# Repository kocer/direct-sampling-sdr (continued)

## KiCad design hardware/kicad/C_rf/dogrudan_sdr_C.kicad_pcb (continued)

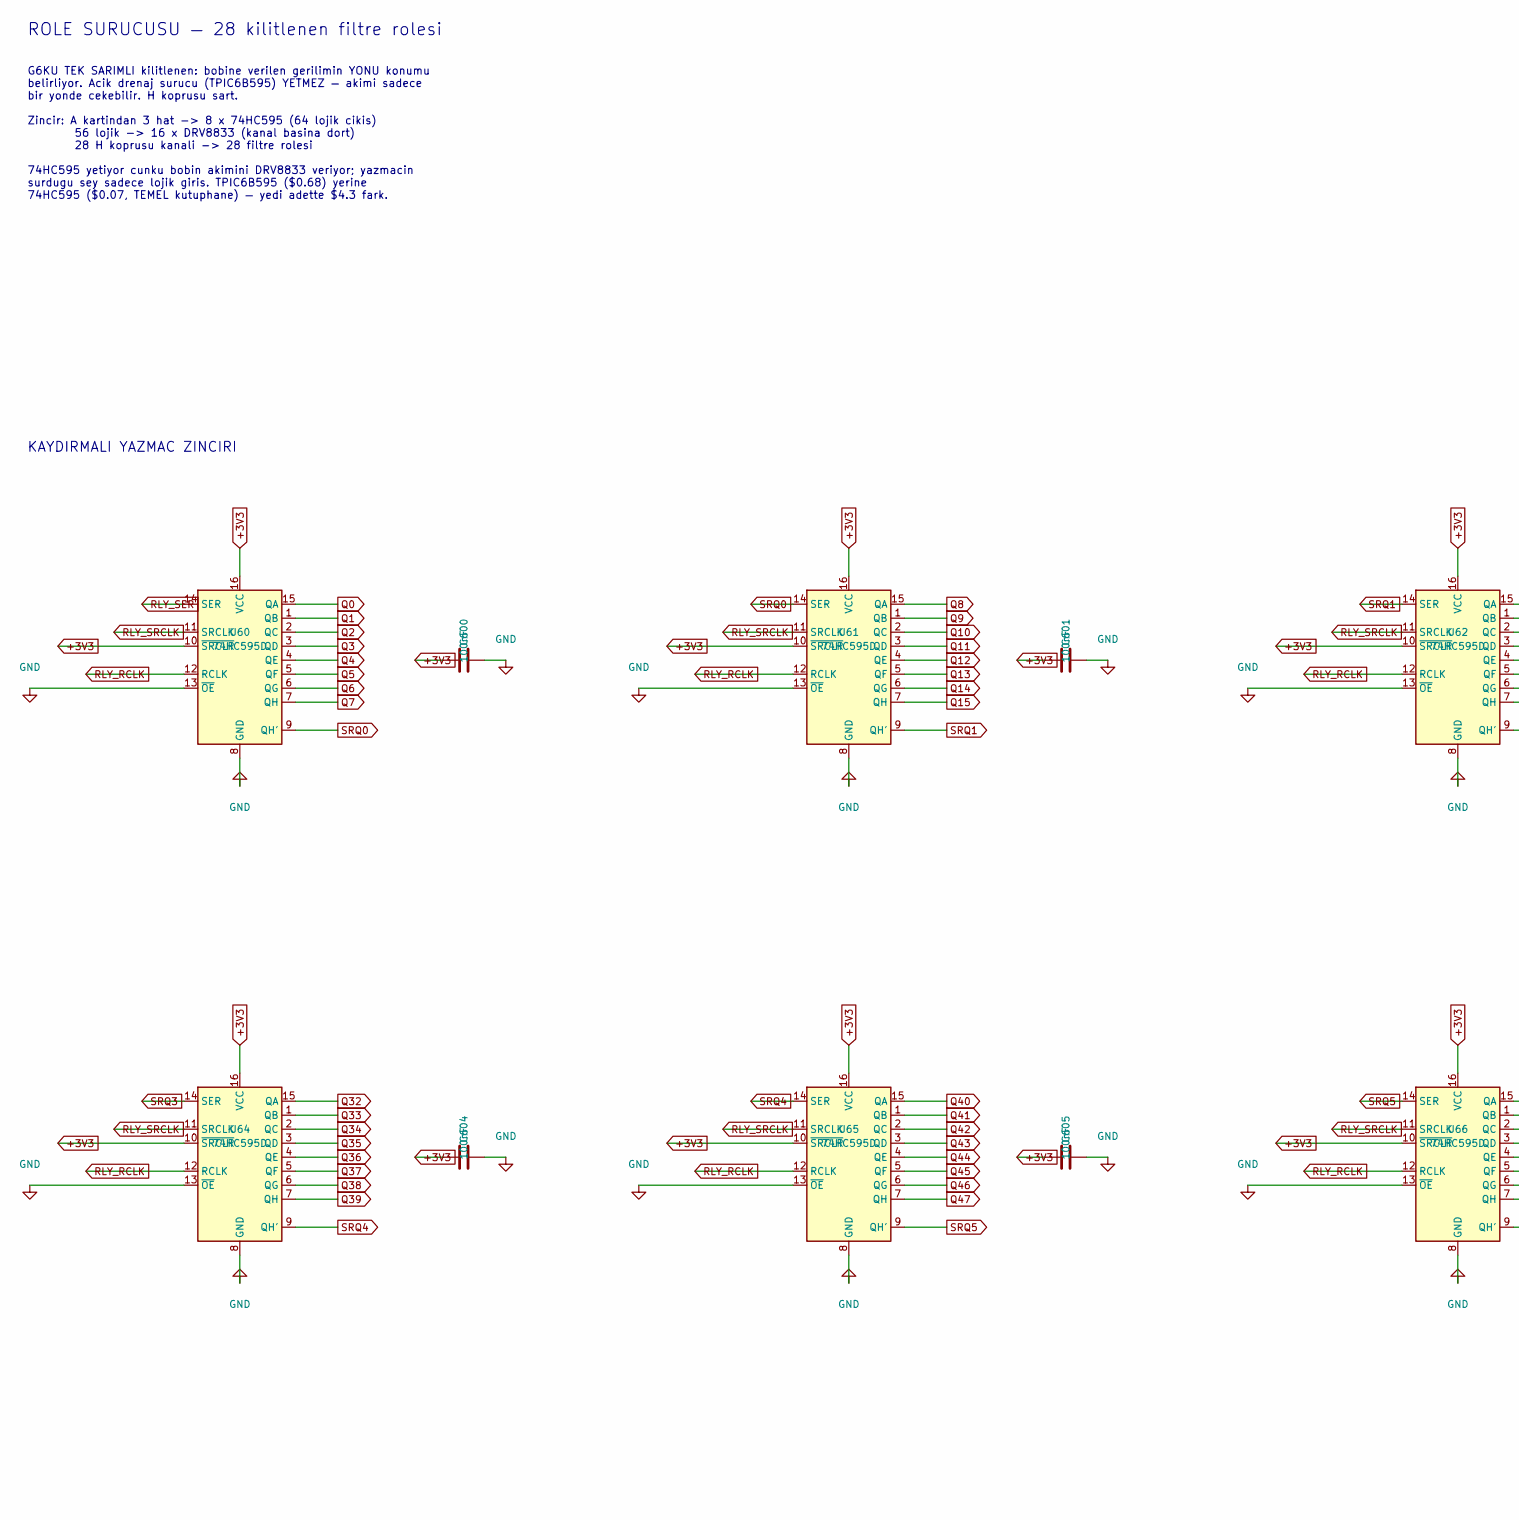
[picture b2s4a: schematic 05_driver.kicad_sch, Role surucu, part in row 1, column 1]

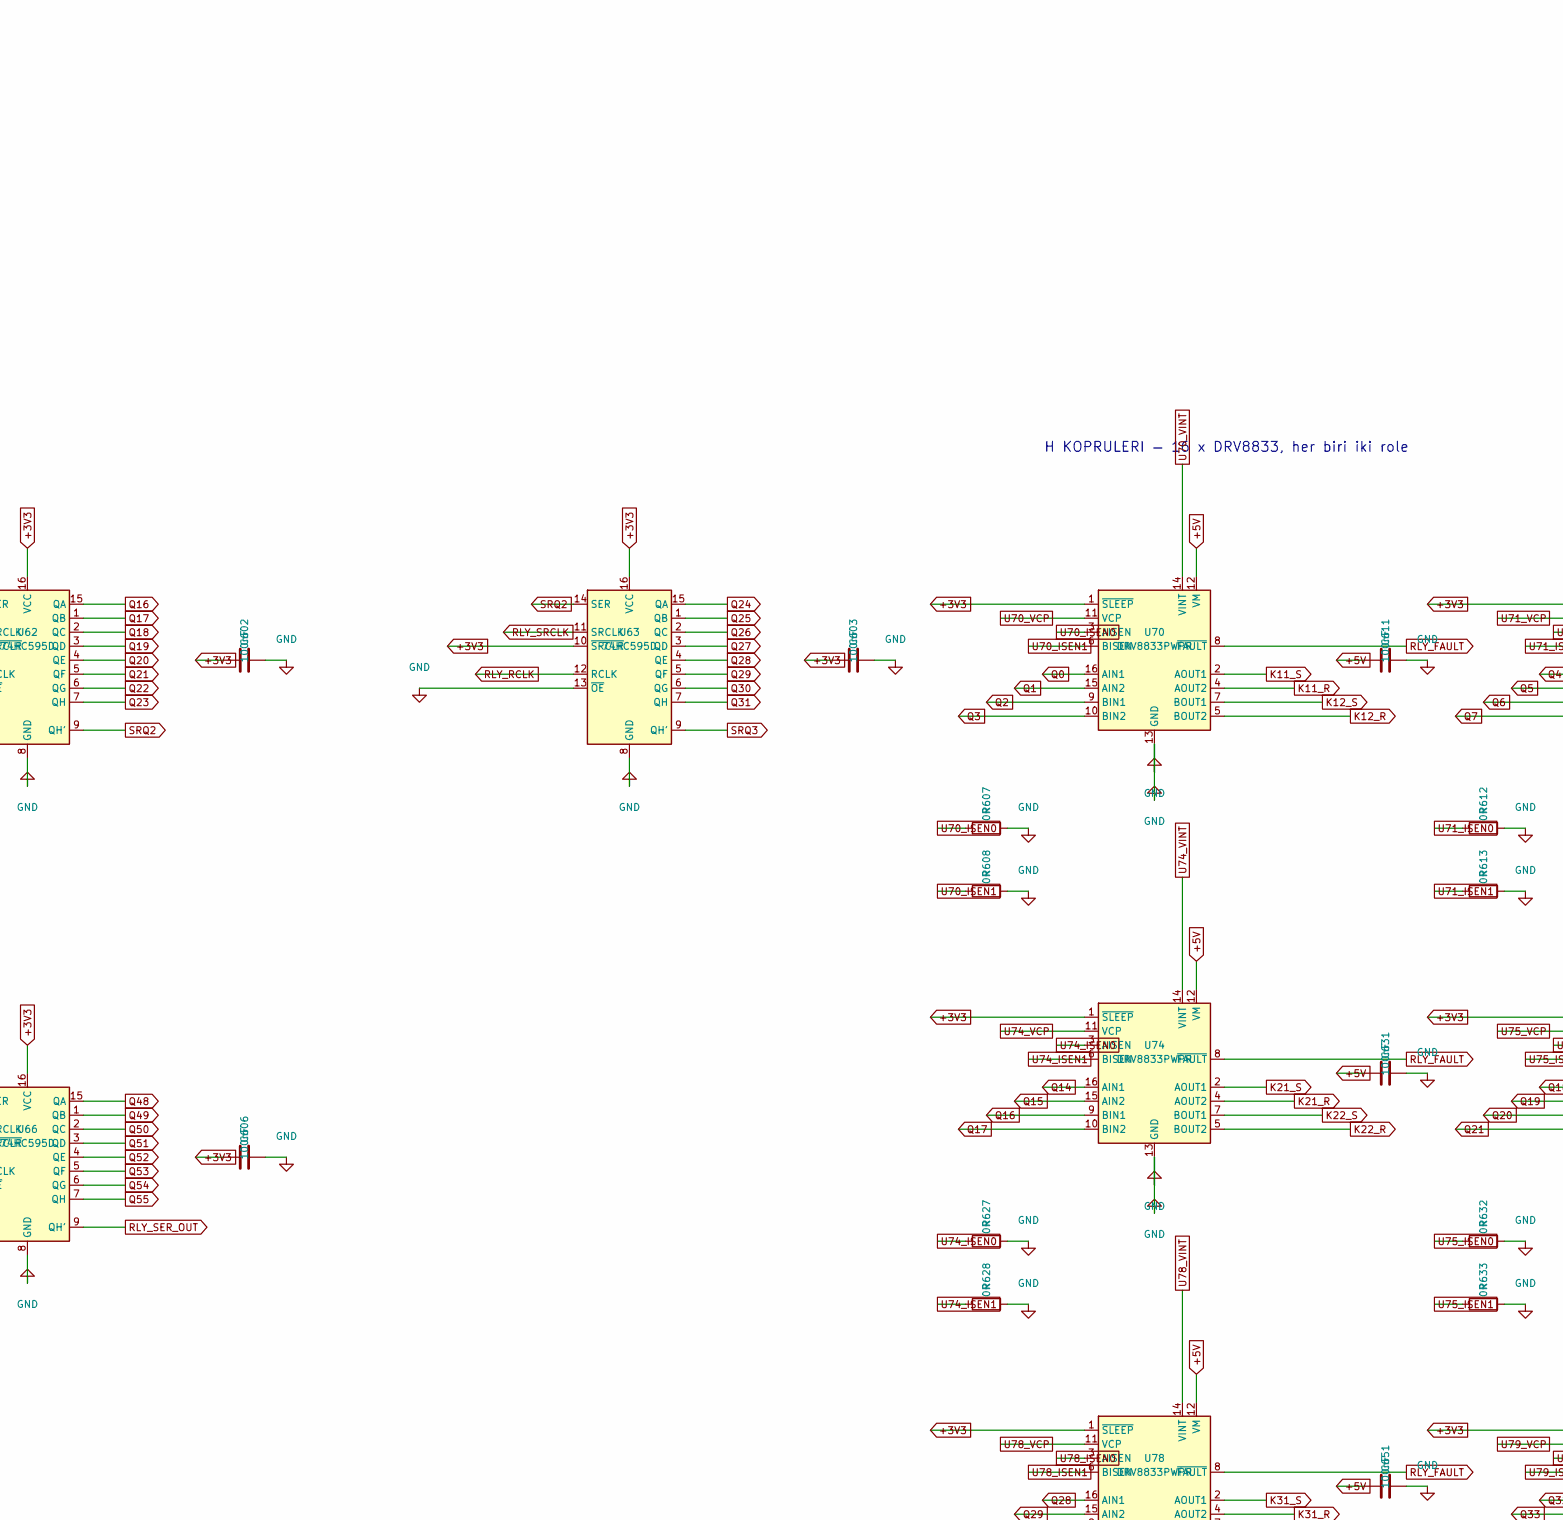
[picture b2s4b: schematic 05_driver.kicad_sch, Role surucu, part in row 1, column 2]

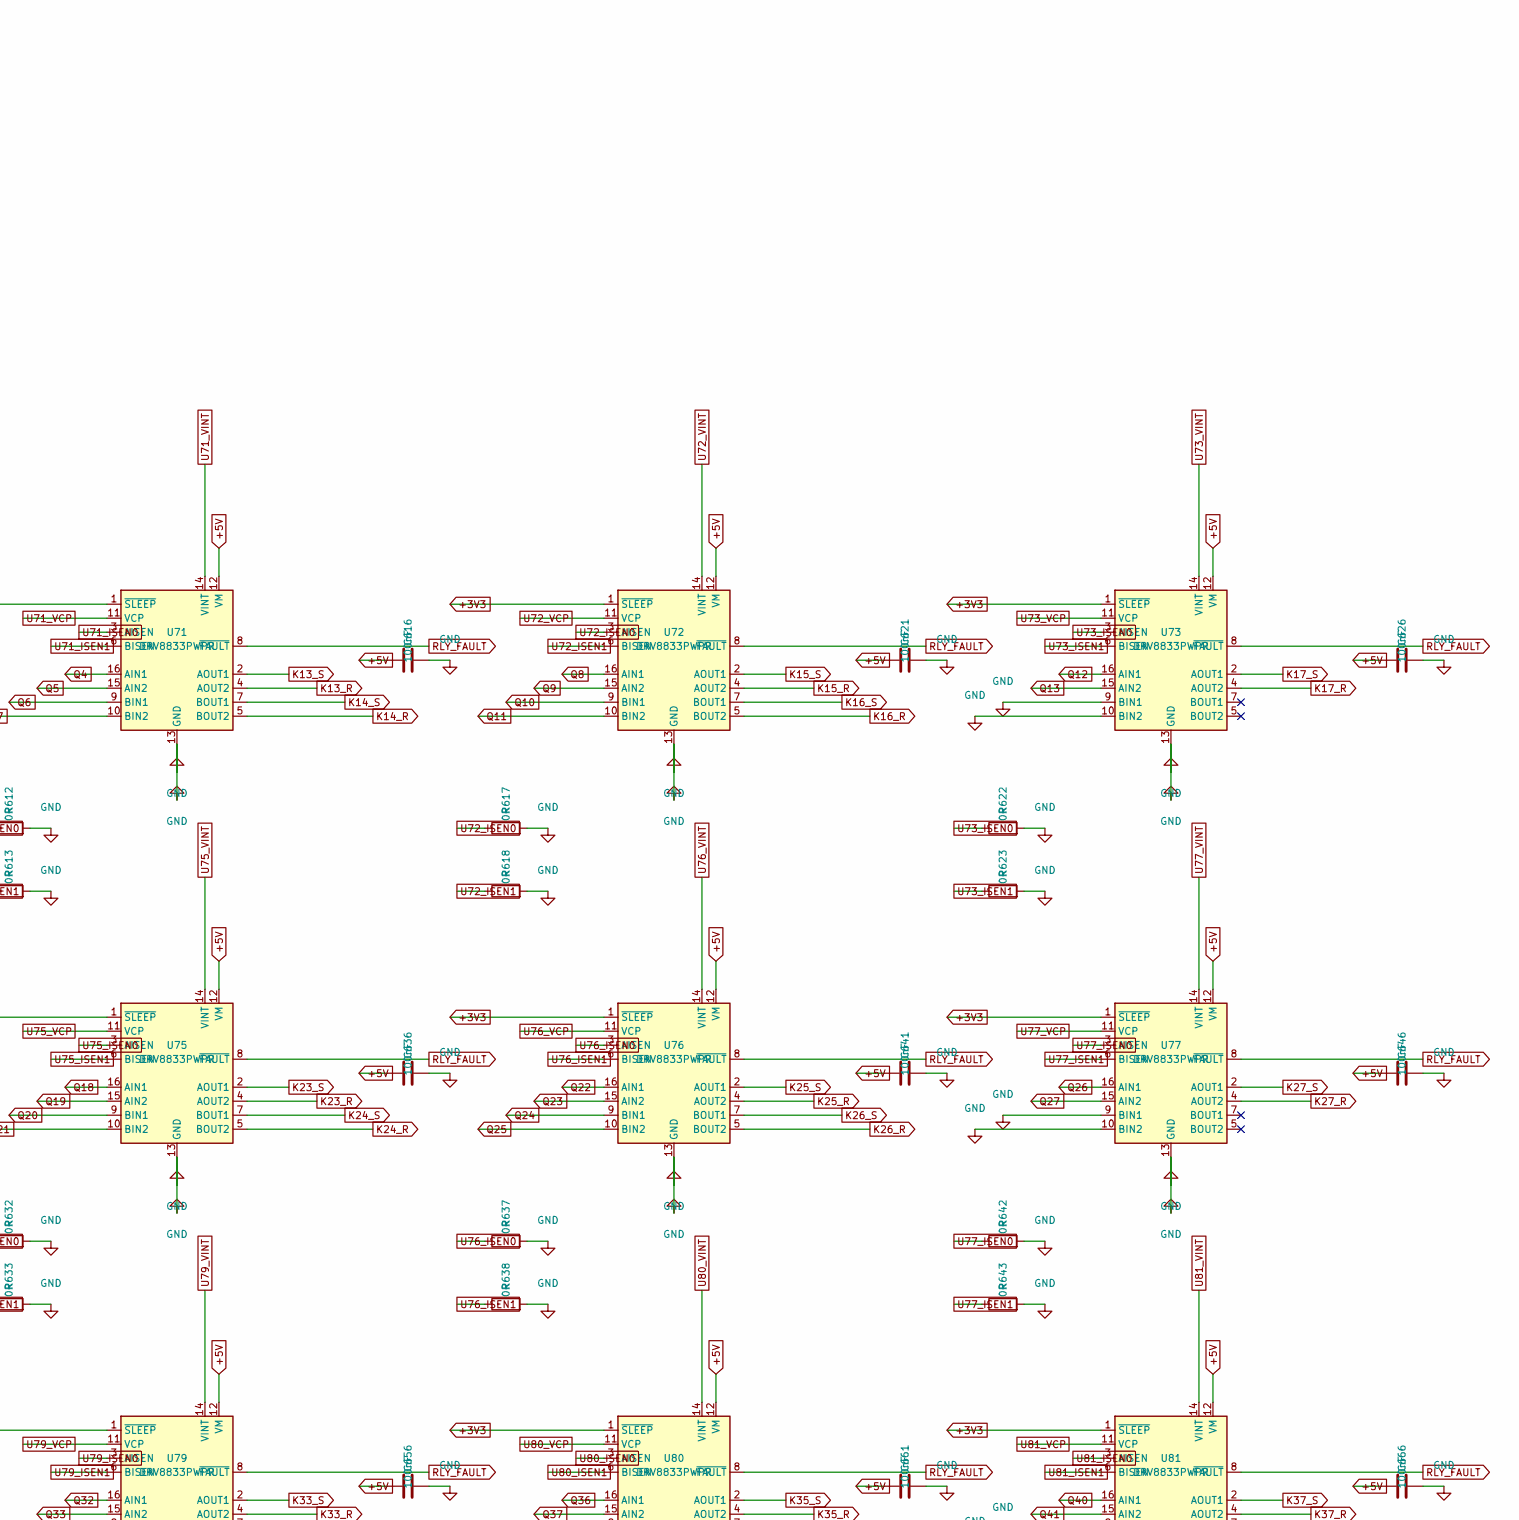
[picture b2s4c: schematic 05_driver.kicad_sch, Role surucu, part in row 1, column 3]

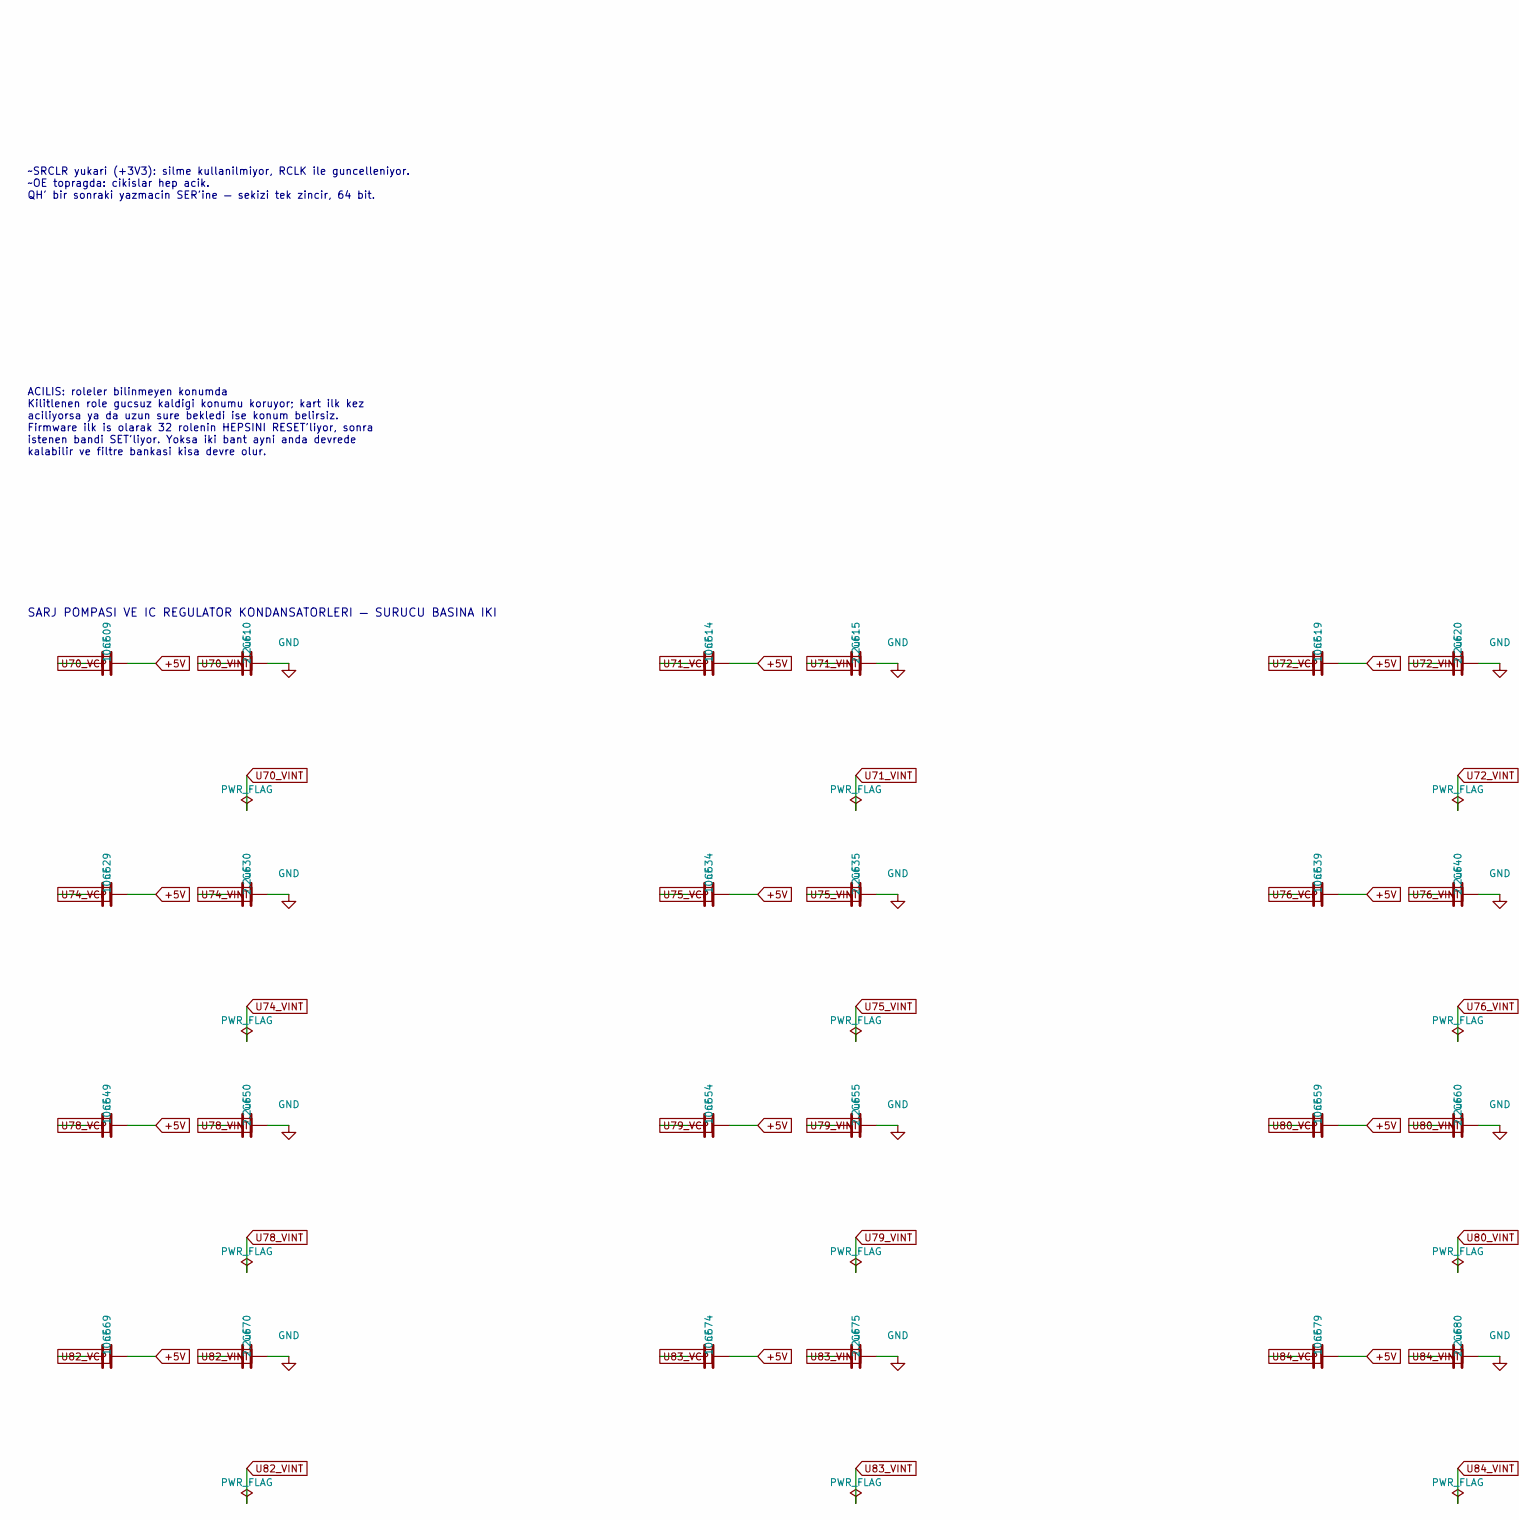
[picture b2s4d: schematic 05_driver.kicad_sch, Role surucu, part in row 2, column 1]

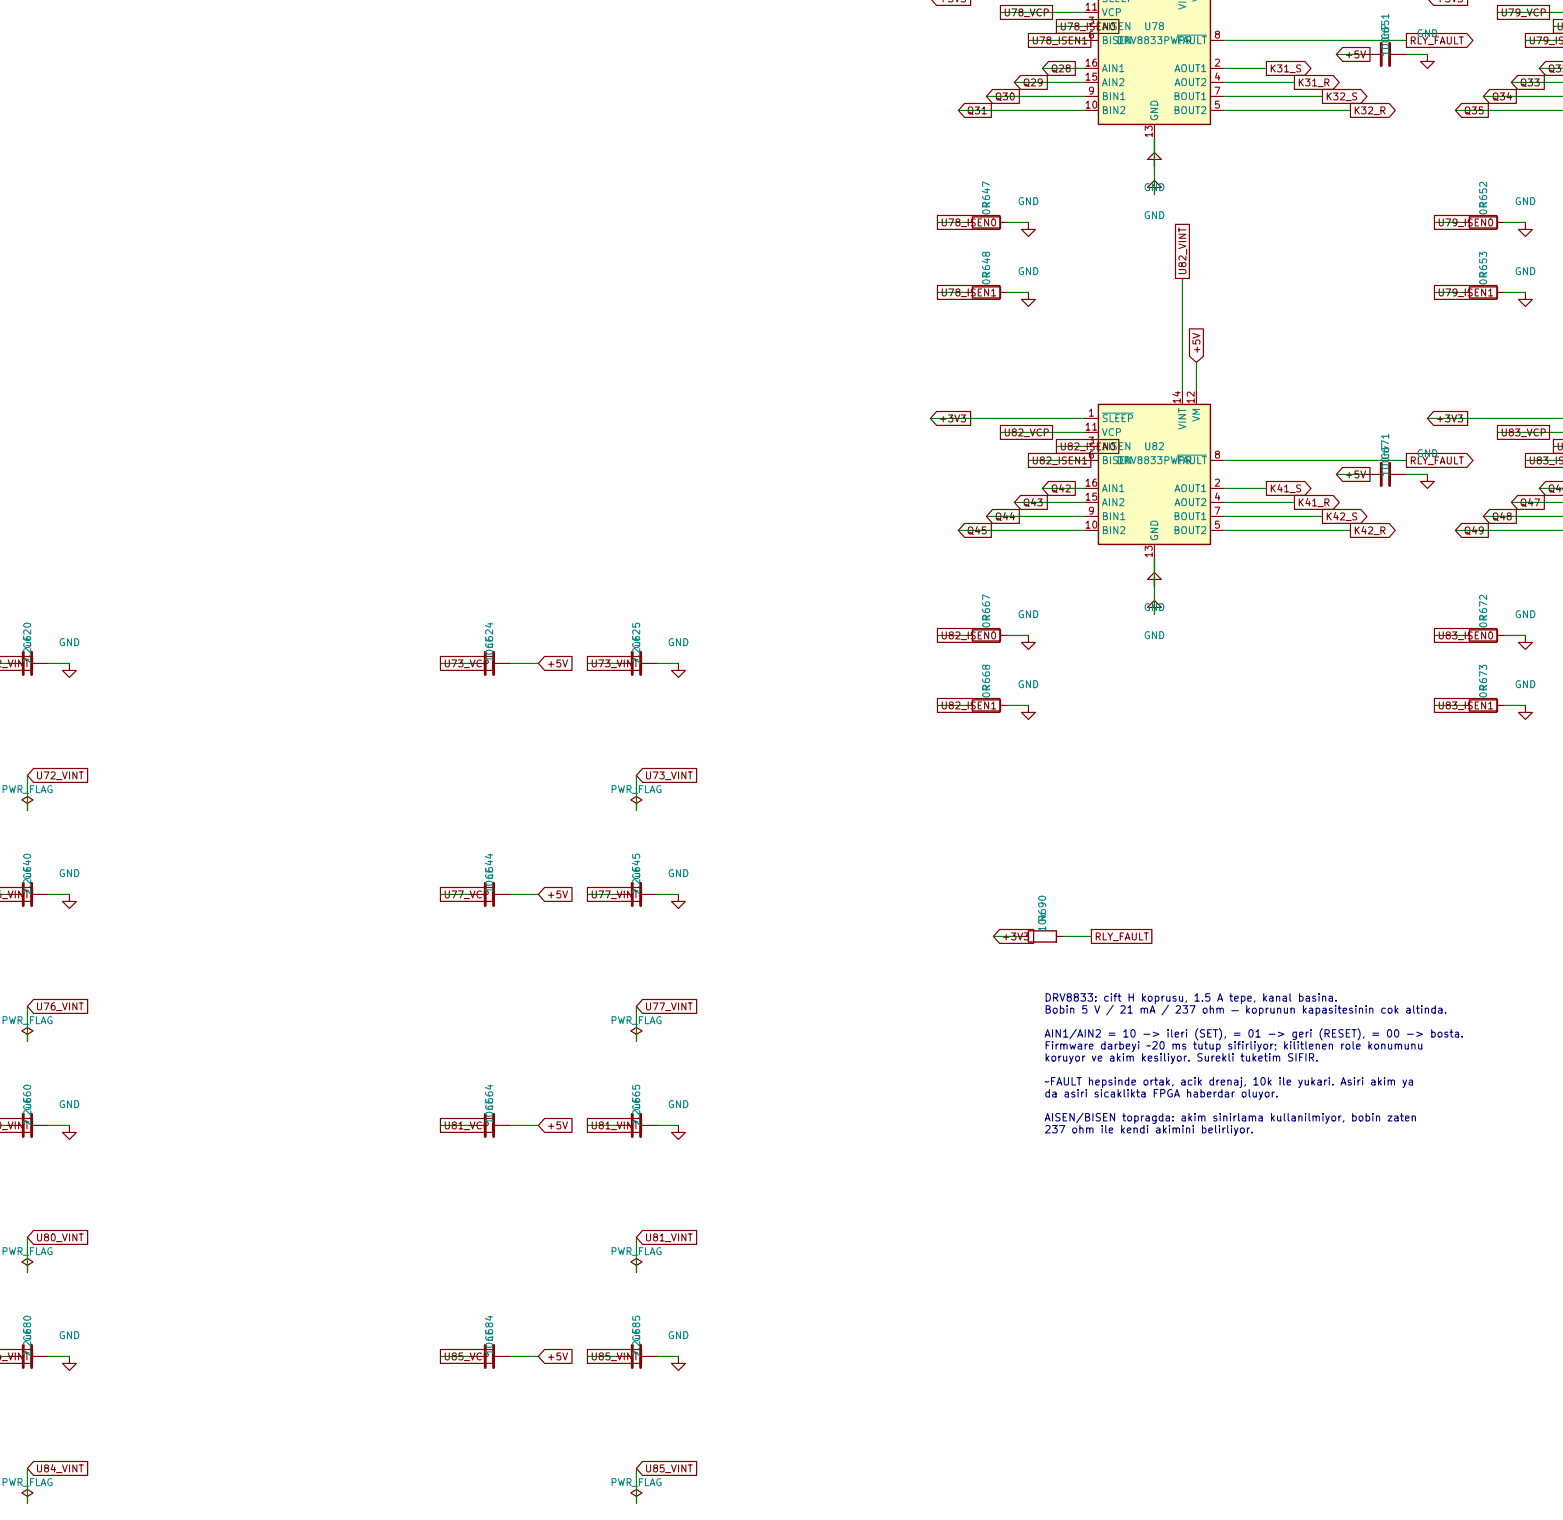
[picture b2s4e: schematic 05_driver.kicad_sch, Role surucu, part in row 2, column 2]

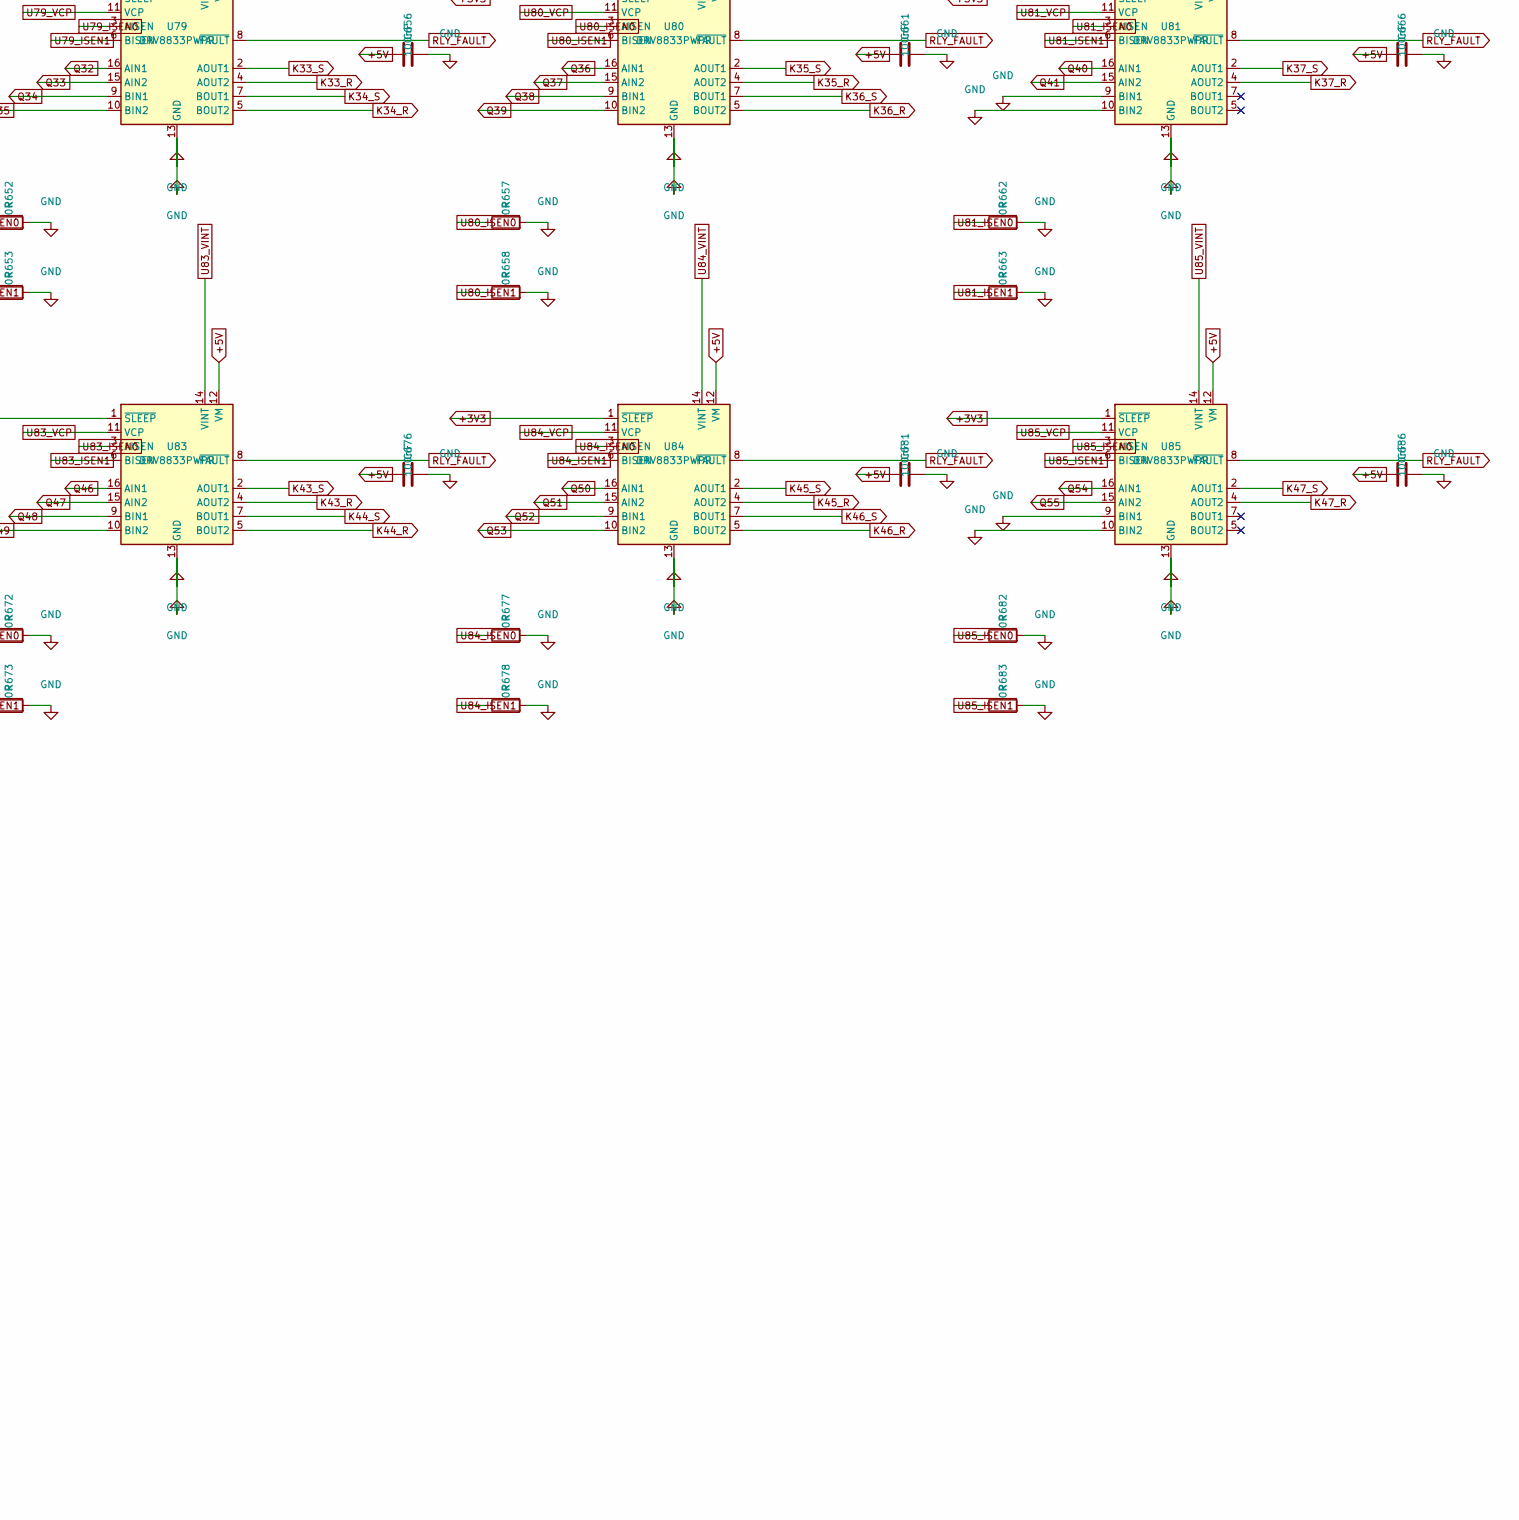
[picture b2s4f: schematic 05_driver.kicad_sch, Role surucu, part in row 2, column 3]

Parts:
C600, C601, C602, C603, C604, C605, C606, C611, C616, C621, C626, C631, C636, C641, C646, C651, C656, C661, C666, C671, C676, C681, C686: 100nF; C_0603_1608Metric
C609, C614, C619, C624, C629, C634, C639, C644, C649, C654, C659, C664, C669, C674, C679, C684: 10nF; C_0603_1608Metric
C610, C615, C620, C625, C630, C635, C640, C645, C650, C655, C660, C665, C670, C675, C680, C685: 2.2uF; C_0603_1608Metric
R607, R608, R612, R613, R617, R618, R622, R623, R627, R628, R632, R633, R637, R638, R642, R643, R647, R648, R652, R653, R657, R658, R662, R663, R667, R668, R672, R673, R677, R678, R682, R683: 0R; R_0603_1608Metric
R690: 10k; R_0603_1608Metric
U60, U61, U62, U63, U64, U65, U66: 74HC595D; SOIC-16_3.9x9.9mm_P1.27mm
U70, U71, U72, U73, U74, U75, U76, U77, U78, U79, U80, U81, U82, U83, U84, U85: DRV8833PWPR; HTSSOP-16-1EP_4.4x5mm_P0.65mm_EP3.4x5mm_Mask2.46x2.31mm_The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

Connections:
+3V3: C600.1, C601.1, C602.1, C603.1, C604.1, C605.1, C606.1, R690.1, U60.10 (~SRCLR), U60.16 (VCC), U61.10 (~SRCLR), U61.16 (VCC), U62.10 (~SRCLR), U62.16 (VCC), U63.10 (~SRCLR), U63.16 (VCC), U64.10 (~SRCLR), U64.16 (VCC), U65.10 (~SRCLR), U65.16 (VCC), U66.10 (~SRCLR), U66.16 (VCC), U70.1 (~SLEEP), U71.1 (~SLEEP), U72.1 (~SLEEP), U73.1 (~SLEEP), U74.1 (~SLEEP), U75.1 (~SLEEP), U76.1 (~SLEEP), U77.1 (~SLEEP), U78.1 (~SLEEP), U79.1 (~SLEEP), U80.1 (~SLEEP), U81.1 (~SLEEP), U82.1 (~SLEEP), U83.1 (~SLEEP), U84.1 (~SLEEP), U85.1 (~SLEEP); also elsewhere on the board
K11_R: U70.4 (AOUT2); also elsewhere on the board
K11_S: U70.2 (AOUT1); also elsewhere on the board
K12_R: U70.5 (BOUT2); also elsewhere on the board
K12_S: U70.7 (BOUT1); also elsewhere on the board
K13_R: U71.4 (AOUT2); also elsewhere on the board
K13_S: U71.2 (AOUT1); also elsewhere on the board
K14_R: U71.5 (BOUT2); also elsewhere on the board
K14_S: U71.7 (BOUT1); also elsewhere on the board
K15_R: U72.4 (AOUT2); also elsewhere on the board
K15_S: U72.2 (AOUT1); also elsewhere on the board
K16_R: U72.5 (BOUT2); also elsewhere on the board
K16_S: U72.7 (BOUT1); also elsewhere on the board
K17_R: U73.4 (AOUT2); also elsewhere on the board
K17_S: U73.2 (AOUT1); also elsewhere on the board
K21_R: U74.4 (AOUT2); also elsewhere on the board
K21_S: U74.2 (AOUT1); also elsewhere on the board
K22_R: U74.5 (BOUT2); also elsewhere on the board
K22_S: U74.7 (BOUT1); also elsewhere on the board
K23_R: U75.4 (AOUT2); also elsewhere on the board
K23_S: U75.2 (AOUT1); also elsewhere on the board
K24_R: U75.5 (BOUT2); also elsewhere on the board
K24_S: U75.7 (BOUT1); also elsewhere on the board
K25_R: U76.4 (AOUT2); also elsewhere on the board
K25_S: U76.2 (AOUT1); also elsewhere on the board
K26_R: U76.5 (BOUT2); also elsewhere on the board
K26_S: U76.7 (BOUT1); also elsewhere on the board
K27_R: U77.4 (AOUT2); also elsewhere on the board
K27_S: U77.2 (AOUT1); also elsewhere on the board
K31_R: U78.4 (AOUT2); also elsewhere on the board
K31_S: U78.2 (AOUT1); also elsewhere on the board
K32_R: U78.5 (BOUT2); also elsewhere on the board
K32_S: U78.7 (BOUT1); also elsewhere on the board
K33_R: U79.4 (AOUT2); also elsewhere on the board
K33_S: U79.2 (AOUT1); also elsewhere on the board
K34_R: U79.5 (BOUT2); also elsewhere on the board
K34_S: U79.7 (BOUT1); also elsewhere on the board
K35_R: U80.4 (AOUT2); also elsewhere on the board
K35_S: U80.2 (AOUT1); also elsewhere on the board
K36_R: U80.5 (BOUT2); also elsewhere on the board
K36_S: U80.7 (BOUT1); also elsewhere on the board
K37_R: U81.4 (AOUT2); also elsewhere on the board
K37_S: U81.2 (AOUT1); also elsewhere on the board
K41_R: U82.4 (AOUT2); also elsewhere on the board
K41_S: U82.2 (AOUT1); also elsewhere on the board
K42_R: U82.5 (BOUT2); also elsewhere on the board
K42_S: U82.7 (BOUT1); also elsewhere on the board
K43_R: U83.4 (AOUT2); also elsewhere on the board
K43_S: U83.2 (AOUT1); also elsewhere on the board
K44_R: U83.5 (BOUT2); also elsewhere on the board
K44_S: U83.7 (BOUT1); also elsewhere on the board
K45_R: U84.4 (AOUT2); also elsewhere on the board
K45_S: U84.2 (AOUT1); also elsewhere on the board
K46_R: U84.5 (BOUT2); also elsewhere on the board
K46_S: U84.7 (BOUT1); also elsewhere on the board
K47_R: U85.4 (AOUT2); also elsewhere on the board
K47_S: U85.2 (AOUT1); also elsewhere on the board
Q0: U60.15 (QA), U70.16 (AIN1)
Q1: U60.1 (QB), U70.15 (AIN2)
Q2: U60.2 (QC), U70.9 (BIN1)
Q3: U60.3 (QD), U70.10 (BIN2)
Q4: U60.4 (QE), U71.16 (AIN1)
Q5: U60.5 (QF), U71.15 (AIN2)
Q6: U60.6 (QG), U71.9 (BIN1)
Q7: U60.7 (QH), U71.10 (BIN2)
Q8: U61.15 (QA), U72.16 (AIN1)
Q9: U61.1 (QB), U72.15 (AIN2)
Q10: U61.2 (QC), U72.9 (BIN1)
Q11: U61.3 (QD), U72.10 (BIN2)
Q12: U61.4 (QE), U73.16 (AIN1)
Q13: U61.5 (QF), U73.15 (AIN2)
Q14: U61.6 (QG), U74.16 (AIN1)
Q15: U61.7 (QH), U74.15 (AIN2)
Q16: U62.15 (QA), U74.9 (BIN1)
Q17: U62.1 (QB), U74.10 (BIN2)
Q18: U62.2 (QC), U75.16 (AIN1)
Q19: U62.3 (QD), U75.15 (AIN2)
Q20: U62.4 (QE), U75.9 (BIN1)
Q21: U62.5 (QF), U75.10 (BIN2)
Q22: U62.6 (QG), U76.16 (AIN1)
Q23: U62.7 (QH), U76.15 (AIN2)
Q24: U63.15 (QA), U76.9 (BIN1)
Q25: U63.1 (QB), U76.10 (BIN2)
Q26: U63.2 (QC), U77.16 (AIN1)
Q27: U63.3 (QD), U77.15 (AIN2)
Q28: U63.4 (QE), U78.16 (AIN1)
Q29: U63.5 (QF), U78.15 (AIN2)
Q30: U63.6 (QG), U78.9 (BIN1)
Q31: U63.7 (QH), U78.10 (BIN2)
Q32: U64.15 (QA), U79.16 (AIN1)
Q33: U64.1 (QB), U79.15 (AIN2)
Q34: U64.2 (QC), U79.9 (BIN1)
Q35: U64.3 (QD), U79.10 (BIN2)
Q36: U64.4 (QE), U80.16 (AIN1)
Q37: U64.5 (QF), U80.15 (AIN2)
Q38: U64.6 (QG), U80.9 (BIN1)
Q39: U64.7 (QH), U80.10 (BIN2)
Q40: U65.15 (QA), U81.16 (AIN1)
Q41: U65.1 (QB), U81.15 (AIN2)
Q42: U65.2 (QC), U82.16 (AIN1)
Q43: U65.3 (QD), U82.15 (AIN2)
Q44: U65.4 (QE), U82.9 (BIN1)
Q45: U65.5 (QF), U82.10 (BIN2)
Q46: U65.6 (QG), U83.16 (AIN1)
Q47: U65.7 (QH), U83.15 (AIN2)
Q48: U66.15 (QA), U83.9 (BIN1)
Q49: U66.1 (QB), U83.10 (BIN2)
Q50: U66.2 (QC), U84.16 (AIN1)
Q51: U66.3 (QD), U84.15 (AIN2)
Q52: U66.4 (QE), U84.9 (BIN1)
Q53: U66.5 (QF), U84.10 (BIN2)
Q54: U66.6 (QG), U85.16 (AIN1)
Q55: U66.7 (QH), U85.15 (AIN2)
RLY_FAULT: R690.2, U70.8 (~FAULT), U71.8 (~FAULT), U72.8 (~FAULT), U73.8 (~FAULT), U74.8 (~FAULT), U75.8 (~FAULT), U76.8 (~FAULT), U77.8 (~FAULT), U78.8 (~FAULT), U79.8 (~FAULT), U80.8 (~FAULT), U81.8 (~FAULT), U82.8 (~FAULT), U83.8 (~FAULT), U84.8 (~FAULT), U85.8 (~FAULT)
RLY_RCLK: U60.12 (RCLK), U61.12 (RCLK), U62.12 (RCLK), U63.12 (RCLK), U64.12 (RCLK), U65.12 (RCLK), U66.12 (RCLK); also elsewhere on the board
RLY_SER: U60.14 (SER); also elsewhere on the board
RLY_SER_OUT: U66.9 (QH'); also elsewhere on the board
RLY_SRCLK: U60.11 (SRCLK), U61.11 (SRCLK), U62.11 (SRCLK), U63.11 (SRCLK), U64.11 (SRCLK), U65.11 (SRCLK), U66.11 (SRCLK); also elsewhere on the board
SRQ0: U60.9 (QH'), U61.14 (SER)
SRQ1: U61.9 (QH'), U62.14 (SER)
SRQ2: U62.9 (QH'), U63.14 (SER)
SRQ3: U63.9 (QH'), U64.14 (SER)
SRQ4: U64.9 (QH'), U65.14 (SER)
SRQ5: U65.9 (QH'), U66.14 (SER)
U70_ISEN0: R607.1, U70.3 (AISEN)
U70_ISEN1: R608.1, U70.6 (BISEN)
U70_VCP: C609.1, U70.11 (VCP)
U71_ISEN0: R612.1, U71.3 (AISEN)
U71_ISEN1: R613.1, U71.6 (BISEN)
U71_VCP: C614.1, U71.11 (VCP)
U72_ISEN0: R617.1, U72.3 (AISEN)
U72_ISEN1: R618.1, U72.6 (BISEN)
U72_VCP: C619.1, U72.11 (VCP)
U73_ISEN0: R622.1, U73.3 (AISEN)
U73_ISEN1: R623.1, U73.6 (BISEN)
U73_VCP: C624.1, U73.11 (VCP)
U74_ISEN0: R627.1, U74.3 (AISEN)
U74_ISEN1: R628.1, U74.6 (BISEN)
U74_VCP: C629.1, U74.11 (VCP)
U75_ISEN0: R632.1, U75.3 (AISEN)
U75_ISEN1: R633.1, U75.6 (BISEN)
U75_VCP: C634.1, U75.11 (VCP)
U76_ISEN0: R637.1, U76.3 (AISEN)
U76_ISEN1: R638.1, U76.6 (BISEN)
U76_VCP: C639.1, U76.11 (VCP)
U77_ISEN0: R642.1, U77.3 (AISEN)
U77_ISEN1: R643.1, U77.6 (BISEN)
U77_VCP: C644.1, U77.11 (VCP)
U78_ISEN0: R647.1, U78.3 (AISEN)
U78_ISEN1: R648.1, U78.6 (BISEN)
U78_VCP: C649.1, U78.11 (VCP)
U79_ISEN0: R652.1, U79.3 (AISEN)
U79_ISEN1: R653.1, U79.6 (BISEN)
U79_VCP: C654.1, U79.11 (VCP)
U80_ISEN0: R657.1, U80.3 (AISEN)
U80_ISEN1: R658.1, U80.6 (BISEN)
U80_VCP: C659.1, U80.11 (VCP)
U81_ISEN0: R662.1, U81.3 (AISEN)
U81_ISEN1: R663.1, U81.6 (BISEN)
U81_VCP: C664.1, U81.11 (VCP)
U82_ISEN0: R667.1, U82.3 (AISEN)
U82_ISEN1: R668.1, U82.6 (BISEN)
U82_VCP: C669.1, U82.11 (VCP)
U83_ISEN0: R672.1, U83.3 (AISEN)
U83_ISEN1: R673.1, U83.6 (BISEN)
U83_VCP: C674.1, U83.11 (VCP)
U84_ISEN0: R677.1, U84.3 (AISEN)
U84_ISEN1: R678.1, U84.6 (BISEN)
U84_VCP: C679.1, U84.11 (VCP)
U85_ISEN0: R682.1, U85.3 (AISEN)
U85_ISEN1: R683.1, U85.6 (BISEN)
U85_VCP: C684.1, U85.11 (VCP)

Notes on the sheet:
SARJ POMPASI VE IC REGULATOR KONDANSATORLERI — SURUCU BASINA IKI
~SRCLR yukari (+3V3): silme kullanilmiyor, RCLK ile guncelleniyor. ~OE topragda: cikislar hep acik. QH' bir sonraki yazmacin SER'ine — sekizi tek zincir, 64 bit.
G6KU TEK SARIMLI kilitlenen: bobine verilen gerilimin YONU konumu belirliyor. Acik drenaj surucu (TPIC6B595) YETMEZ — akimi sadece bir yonde cekebilir. H koprusu sart. Zincir: A kartindan 3 hat -> 8 x 74HC595 (64 lojik cikis) 56 lojik -> 16 x DRV8833 (kanal basina dort) 28 H koprusu kanali -> 28 fi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
KAYDIRMALI YAZMAC ZINCIRI
ACILIS: roleler bilinmeyen konumda Kilitlenen role gucsuz kaldigi konumu koruyor; kart ilk kez aciliyorsa ya da uzun sure bekledi ise konum belirsiz. Firmware ilk is olarak 32 rolenin HEPSINI RESET'liyor, sonra istenen bandi SET'liyor. Yoksa iki bant ayni anda devrede kalabilir ve filtre bankasi ki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
H KOPRULERI — 16 x DRV8833, her biri iki role
DRV8833: cift H koprusu, 1.5 A tepe, kanal basina. Bobin 5 V / 21 mA / 237 ohm — koprunun kapasitesinin cok altinda. AIN1/AIN2 = 10 -> ileri (SET), = 01 -> geri (RESET), = 00 -> bosta. Firmware darbeyi ~20 ms tutup sifirliyor; kilitlenen role konumunu koruyor ve akim kesiliyor. Surekli tuketim SIFI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
ROLE SURUCUSU — 28 kilitlenen filtre rolesi

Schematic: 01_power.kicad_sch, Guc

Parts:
C80, C81: 22uF; C_0603_1608Metric
C82, C84: 100nF; C_0603_1608Metric
C83: 10uF; C_1206_3216Metric
L80: 2.2uH; L_Taiyo-Yuden_NR-30xx
R80: 105k; R_0603_1608Metric
R81: 20k; R_0603_1608Metric
U90: TPS62130; VQFN-16-1EP_3x3mm_P0.5mm_EP1.68x1.68mm

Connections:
FB_U90: R80.2, R81.1, U90.5 (FB)
unnamed: L80.1, U90.1 (SW), U90.2 (SW), U90.3 (SW)

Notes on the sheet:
Iki ray geliyor: VIN_PROT (9-17 V) ve +3V3, ikisi de A kartindan kart arasi bagliktan. Burada uretilen tek sey role bobinlerinin +5V'u.
GUC BUTCESI
A KARTINDAN GELEN RAYLAR
+5V — role bobinleri
Vout = 0.8 x (1 + R80/R81). 5 V icin oran 5.25 -> 105k / 20k. NEDEN BUCK, LDO DEGIL: girisin tavani 18 V. LDO ile 18->5 dusurmek 13 V x akim kadar isi demek. Kilitlenen role akimi darbeli ama darbe aninda 32 bobinden biri 21 mA cekiyor, ve firmware istese ard arda darbeleyebilir.
9-17 V, A kartinda ters polarite korumali
Bayraklar gercek baglanti degil: raylar konnektorden geliyor, bu kartta bir guc kaynagi pini yok, ERC onu boyle ogreniyor.
SUREKLI: PE4312 x4 4 x 0.6 mA @3V3 = 2.4 mA ~8 mW 74HC595 x8 ihmal edilebilir DRV8833 x16 uyku disi ~2 mA = 32 mA ~106 mW TOPLAM ~115 mW DARBELI (role anahtarlama, ~20 ms): bir bobin 5 V / 21 mA = 105 mW firmware tek tek darbeliyor, es zamanli degil KILITLENEN ROLENIN KAZANCI: normal role olsaydi d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
PE4312 VDD, 74HC595 ve DRV8833 lojik
C KARTI GUCU

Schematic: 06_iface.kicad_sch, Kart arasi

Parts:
J80: A kartina; PinHeader_2x10_P2.54mm_Vertical
J81: A kartina #2; PinHeader_1x06_P2.54mm_Vertical
J82: RX1 -> A; SMA_Amphenol_132289_EdgeMount
J83: RX2 -> A; SMA_Amphenol_132289_EdgeMount
J84: RX3 -> A; SMA_Amphenol_132289_EdgeMount
J85: RX4 -> A; SMA_Amphenol_132289_EdgeMount
J86: TX1 <- A; SMA_Amphenol_132289_EdgeMount
J87: TX2 <- A; SMA_Amphenol_132289_EdgeMount
J88: TX3 <- A; SMA_Amphenol_132289_EdgeMount
J89: TX4 <- A; SMA_Amphenol_132289_EdgeMount
J90: D kartina; PinHeader_1x06_P2.54mm_Vertical
R90: 0R; R_0603_1608Metric

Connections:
+3V3: J80.1, J81.5, J90.4; also elsewhere on the board
ATT1_LE: J80.19; also elsewhere on the board
ATT2_LE: J81.1; also elsewhere on the board
ATT3_LE: J81.2; also elsewhere on the board
ATT4_LE: J81.3; also elsewhere on the board
ATT_CLK: J80.18; also elsewhere on the board
ATT_DATA: J80.17; also elsewhere on the board
GND_HDR: J80.2, J80.4, J80.6, J80.8, J80.10, J80.12, J80.14, J80.16, R90.1
RLY_RCLK: J80.7, J90.3; also elsewhere on the board
RLY_SER: J80.3; also elsewhere on the board
RLY_SER_OUT: J90.1; also elsewhere on the board
RLY_SRCLK: J80.5, J90.2; also elsewhere on the board
RX1_OUT: J82.1 (In); also elsewhere on the board
RX2_OUT: J83.1 (In); also elsewhere on the board
RX3_OUT: J84.1 (In); also elsewhere on the board
RX4_OUT: J85.1 (In); also elsewhere on the board
TR1: J80.9; also elsewhere on the board
TR2: J80.11; also elsewhere on the board
TR3: J80.13; also elsewhere on the board
TR4: J80.15; also elsewhere on the board
TX1: J86.1 (In); also elsewhere on the board
TX2: J87.1 (In); also elsewhere on the board
TX3: J88.1 (In); also elsewhere on the board
TX4: J89.1 (In); also elsewhere on the board

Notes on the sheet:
J80 — ana baslik (A kartindaki J63'un karsisi)
YAZMAC ZINCIRI -> D KARTI
A KARTI GUNCELLENDI — arayuz artik eslesiyor. Onceden A'da ATT1_DATA/CLK/LE + ATT2_DATA/CLK/LE vardi (iki zayiflatici varsayimi). Dort zayiflatici olunca veri ve saat ortaklasti, LE'ler ayrildi. Hat sayisi ayni (6), anlami degisti. A kartinda 08_control bu sayfaya gore yeniden yazildi.
Dort alis cikisi (zayiflaticidan sonra) A kartinin SMA girislerine, dort veris girisi A kartinin DAC cikislarindan. SMA kart-arasi pahali ama sinyal butunlugu icin dogru secim: 2.54 mm baslikta empedans kontrolu yok, dort kanalin faz uyumu orada bozulur. Kisa RG316 kuyruklar, ES BOY kesilmis. ** ES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
KART ARASI — A <-> C
D KARTINA (PA) — ileride
J81 — ikinci baslik (A kartindaki J65)
RF — koaks kuyruk, baslik DEGIL
C kartindaki yedi 74HC595'in sonuncusunun QH' cikisi D kartinin LPF yazmacina gidiyor: tek zincir, sekiz yazmac, 64 bit. Saat ve mandal hatlari ortak. D kartina ayri seri hat cekmeye gerek yok; ikisi de yavas role kontrolu.
Dijital hatlar baslikta, RF koaks kuyrukla. Baslikla RF gecirmek kart arasi empedansi bozar ve komsu hatlara kuple olur.
PA gelince TX1 yolu C kartindan gecmeyecek: DAC -> D karti surucu -> final -> D kartinin kendi anten anahtari -> anten. C kartinin T/R'i o portta devre disi kalir (milivat rolesi 100 W anahtarlayamaz, NETLIST_C.md §3 notu). DPD geri besleme yolu buradan gececek: D kartindaki kuplor -> zayiflatici -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
